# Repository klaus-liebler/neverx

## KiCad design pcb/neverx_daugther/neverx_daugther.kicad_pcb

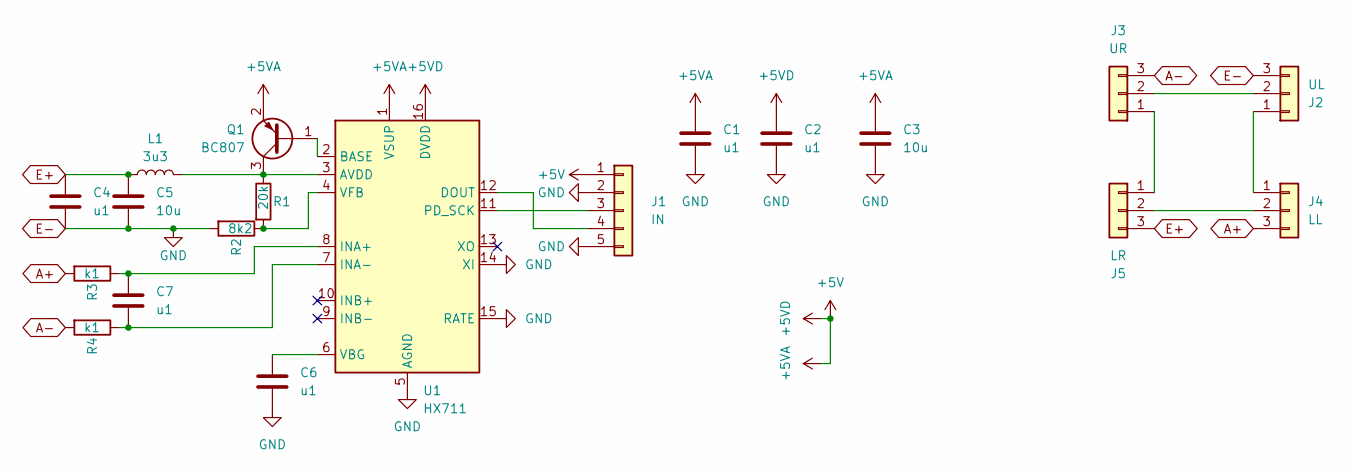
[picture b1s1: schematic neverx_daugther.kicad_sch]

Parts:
C1, C2, C4, C6, C7: u1; C_0805_2012Metric_Pad1.18x1.45mm_HandSolder
C3, C5: 10u; C_0805_2012Metric_Pad1.18x1.45mm_HandSolder
J1: IN; M12-5
J2: UL; JST_XH_B3B-XH-A_1x03_P2.50mm_Vertical
J3: UR; JST_XH_B3B-XH-A_1x03_P2.50mm_Vertical
J4: LL; JST_XH_B3B-XH-A_1x03_P2.50mm_Vertical
J5: LR; JST_XH_B3B-XH-A_1x03_P2.50mm_Vertical
L1: 3u3; L_0805_2012Metric_Pad1.15x1.40mm_HandSolder
Q1: BC807; SOT-23_Handsoldering
R1: 20k; R_0805_2012Metric_Pad1.20x1.40mm_HandSolder
R2: 8k2; R_0805_2012Metric_Pad1.20x1.40mm_HandSolder
R3, R4: k1; R_0805_2012Metric_Pad1.20x1.40mm_HandSolder
U1: HX711; SOIC-16_3.9x9.9mm_P1.27mm

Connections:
+5V: C1.1, C2.1, C3.1, J1.1, Q1.2 (E), U1.1 (VSUP), U1.16 (DVDD)
A+: J4.3, R3.2
A-: J3.3, R4.2
E+: C4.1, C5.1, J5.3, L1.1
E-: C1.2, C2.2, C3.2, C4.2, C5.2, C6.2, J1.2, J1.5, J2.3, R2.2, U1.5 (AGND), U1.14 (XI), U1.15 (RATE)
unnamed: J1.3, U1.11 (PD_SCK)
unnamed: J1.4, U1.12 (DOUT)
unnamed: J2.1, J4.1
unnamed: J2.2, J3.2
unnamed: J3.1, J5.1
unnamed: J4.2, J5.2
unnamed: Q1.1 (B), U1.2 (BASE)
unnamed: L1.2, Q1.3 (C), R1.1, U1.3 (AVDD)
unnamed: C7.1, R3.1, U1.8 (INA+)
unnamed: C7.2, R4.1, U1.7 (INA-)
unnamed: C6.1, U1.6 (VBG)
unnamed: R1.2, R2.1, U1.4 (VFB)

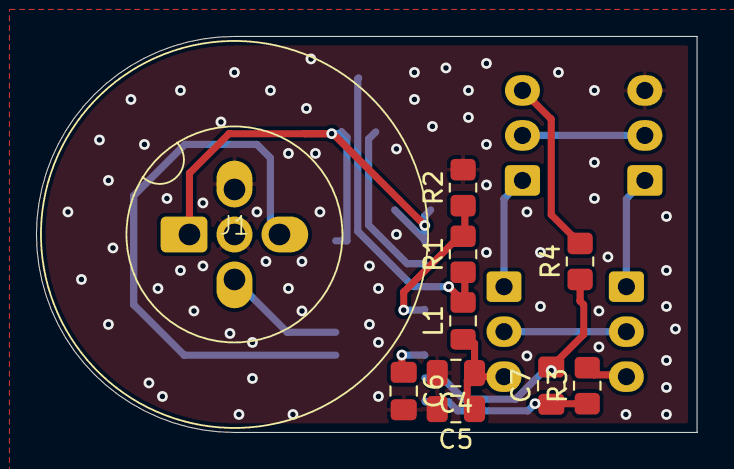
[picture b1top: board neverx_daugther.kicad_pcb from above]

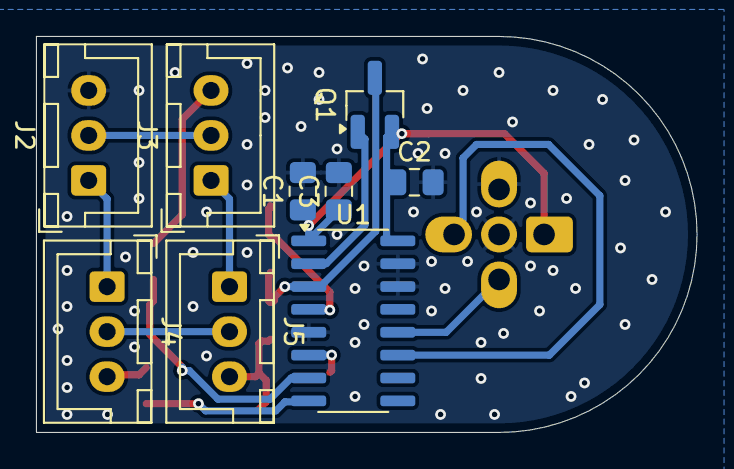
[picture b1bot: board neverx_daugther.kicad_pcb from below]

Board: 2 copper layers, 36.7 x 22.0 mm, 19 parts (9 on the bottom side), 17 nets.

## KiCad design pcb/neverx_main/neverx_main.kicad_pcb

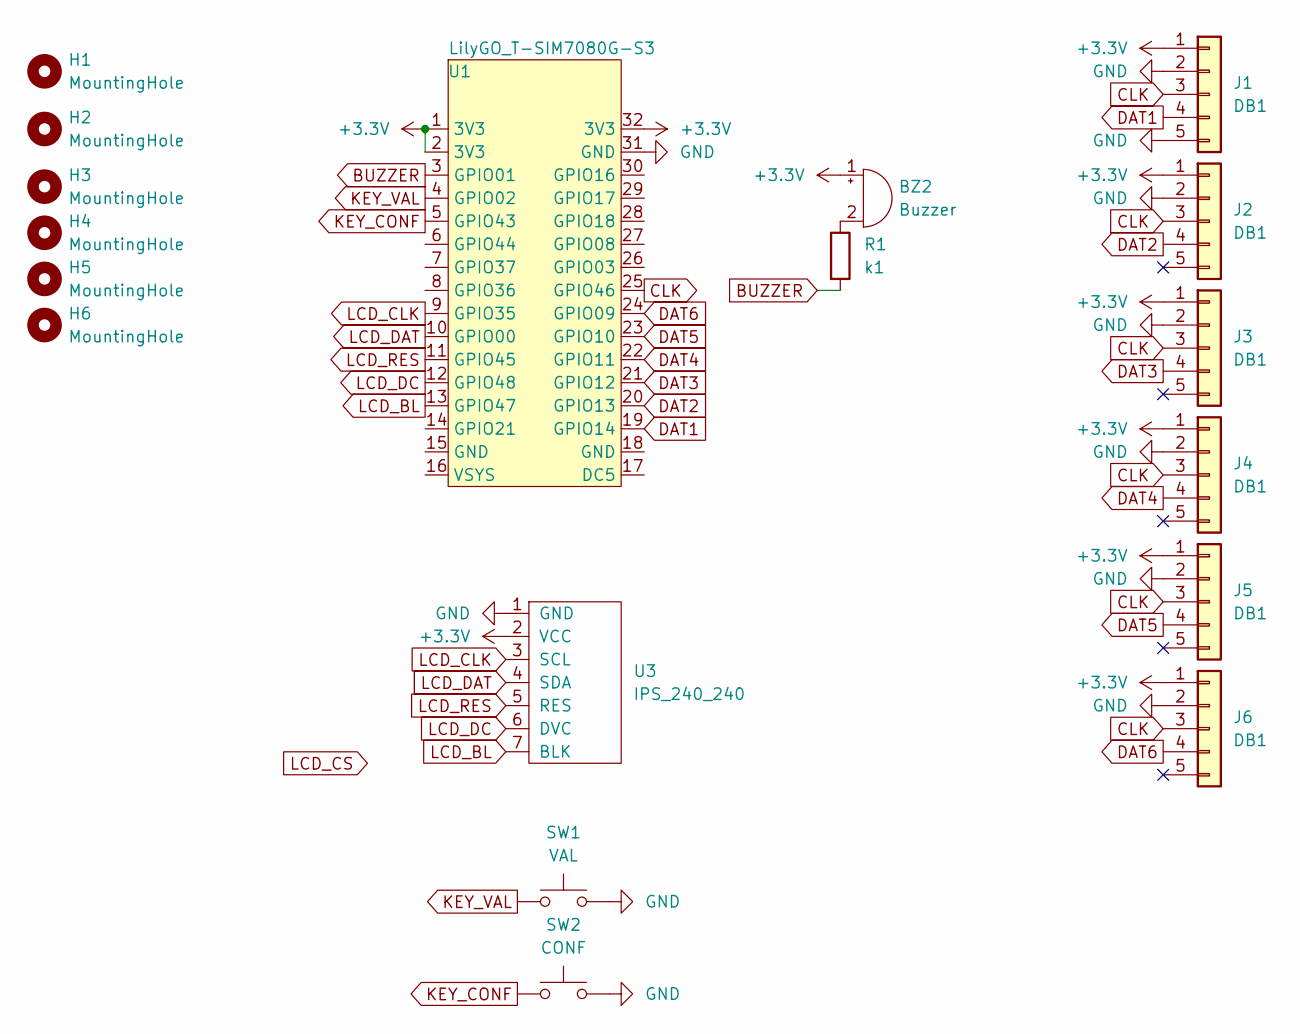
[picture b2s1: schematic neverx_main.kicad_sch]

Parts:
BZ2: Buzzer; Buzzer_12x9.5RM6.6
H1, H2, H3, H4, H5, H6: MountingHole; MountingHole_3.2mm_M3
J1, J2, J3, J4, J5, J6: DB1; M12-5
R1: k1; R_0805_2012Metric_Pad1.20x1.40mm_HandSolder
SW1: VAL; SW_PUSH_6mm
SW2: CONF; SW_PUSH_6mm
U1: LilyGO_T-SIM7080G-S3
U3: IPS_240_240; IPS_240_240_1.3

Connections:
+3.3V: BZ2.1 (+), J1.1, J2.1, J3.1, J4.1, J5.1, J6.1, U1.1 (3V3), U1.2 (3V3), U1.32 (3V3), U3.2 (VCC)
BUZZER: R1.2, U1.3 (GPIO01)
CLK: J1.3, J2.3, J3.3, J4.3, J5.3, J6.3, U1.25 (GPIO46)
DAT1: J1.4, U1.19 (GPIO14)
DAT2: J2.4, U1.20 (GPIO13)
DAT3: J3.4, U1.21 (GPIO12)
DAT4: J4.4, U1.22 (GPIO11)
DAT5: J5.4, U1.23 (GPIO10)
DAT6: J6.4, U1.24 (GPIO09)
GND: J1.2, J1.5, J2.2, J3.2, J4.2, J5.2, J6.2, SW1.2, SW2.2, U1.31 (GND), U3.1 (GND)
KEY_CONF: SW2.1, U1.5 (GPIO43)
KEY_VAL: SW1.1, U1.4 (GPIO02)
LCD_BL: U1.13 (GPIO47), U3.7 (BLK)
LCD_CLK: U1.9 (GPIO35), U3.3 (SCL)
LCD_DAT: U1.10 (GPIO00), U3.4 (SDA)
LCD_DC: U1.12 (GPIO48), U3.6 (DVC)
LCD_RES: U1.11 (GPIO45), U3.5 (RES)
unnamed: BZ2.2 (-), R1.1

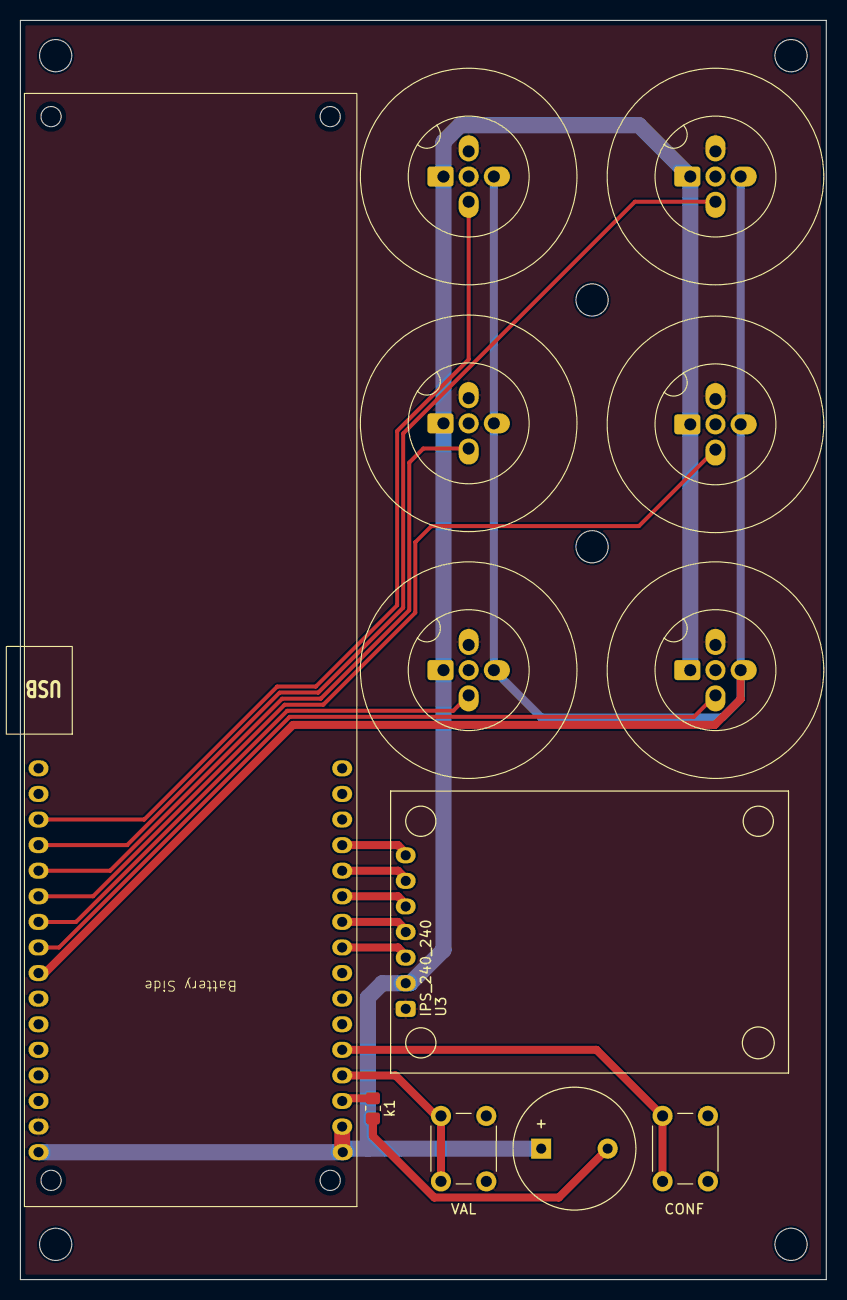
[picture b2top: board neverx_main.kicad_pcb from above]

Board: 2 copper layers, 80.0 x 125.0 mm, 18 parts (0 on the bottom side), 18 nets.

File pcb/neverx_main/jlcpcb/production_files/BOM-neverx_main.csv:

Comment,Designator,Footprint,LCSC,Quantity
Buzzer,BZ2,Buzzer_12x9.5RM6.6,,1
k1,R1,R_0805_2012Metric_Pad1.20x1.40mm_HandSolder,,1
DB1,J1,M12-5,,1
VAL,SW1,SW_PUSH_6mm,,1
DB1,J4,M12-5,,1
DB1,J3,M12-5,,1
DB1,J5,M12-5,,1
DB1,J2,M12-5,,1
IPS_240_240,U3,IPS_240_240_1.3,,1
LilyGO_T-SIM7080G-S3,U1,LilyGO_T-SIM7080G-S3,,1
CONF,SW2,SW_PUSH_6mm,,1
DB1,J6,M12-5,,1

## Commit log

2025-09-29 Initial
2025-12-01 As ordered @ JLCPCB
2025-12-11 Fixed wrongtraces
2026-02-24 As ordered @JLCPCB
